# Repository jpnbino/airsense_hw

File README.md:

# Air Sense - Hardware

O projeto Air Sense foi desenvolvido para medir a qualidade do ar em centros urbanos. Para isso hardware desenvolvido conta com uma série de sensores capazes de identificar certos tipos de gases no ambiente, tais como, CO e NO2.

Este repositório contém os arquivos fontes do projeto de Hardware.

---

## Detalhes de Hardware

|  Item           |Descrição |
|-----------------|------------|
| Tensão de entrada   |  9V - 25V    |
| Tamanho da placa      | 16.5mm x 31mm|
| Controlador principal            | STM32F108 |
| Módulo GSM       | SIM800L            |
| Sensor de umidade, temperatura e pressão       | BME280            |
| Sensor de CO, NO2 e NH3        | MICS 6814            |

---

## Versão

V1I1 - Versão Inicial.

---

## Equipe

Rauhe - [rauhe.abdelhamid@gmail.com]()

João Paulo - [jpnogg@gmail.com]()

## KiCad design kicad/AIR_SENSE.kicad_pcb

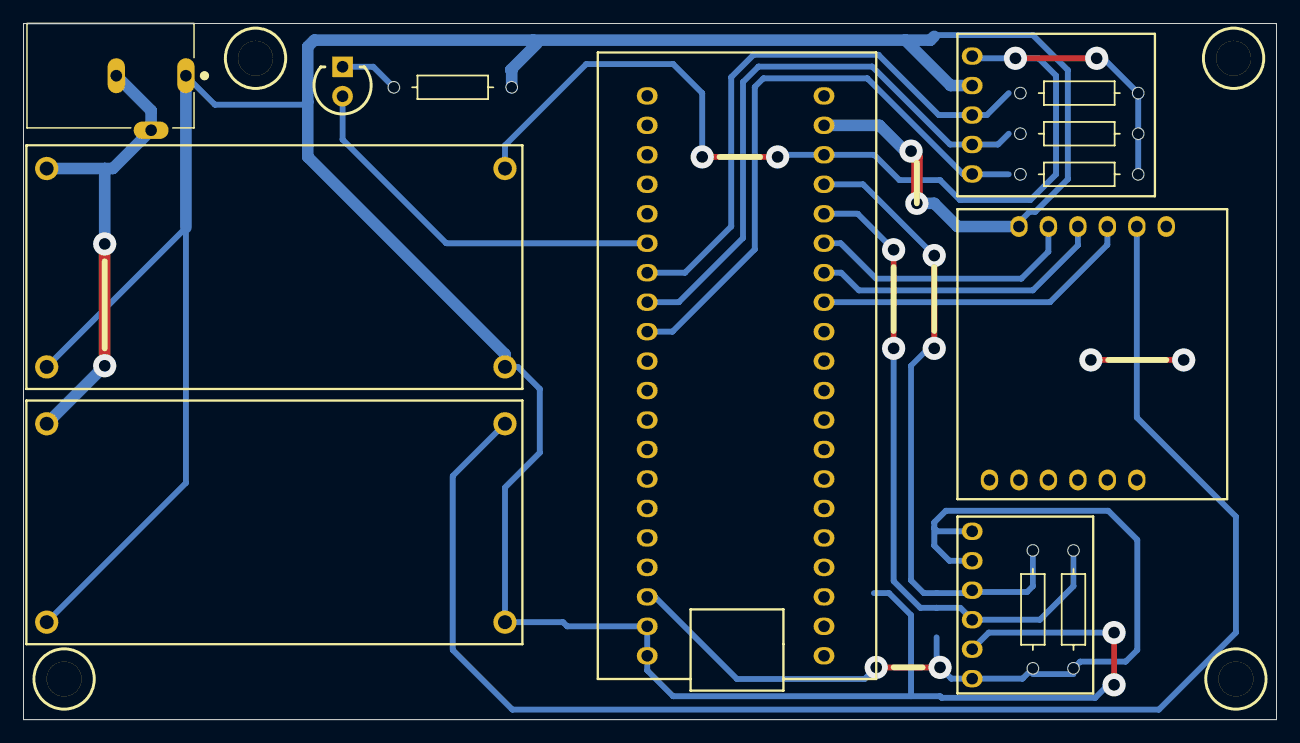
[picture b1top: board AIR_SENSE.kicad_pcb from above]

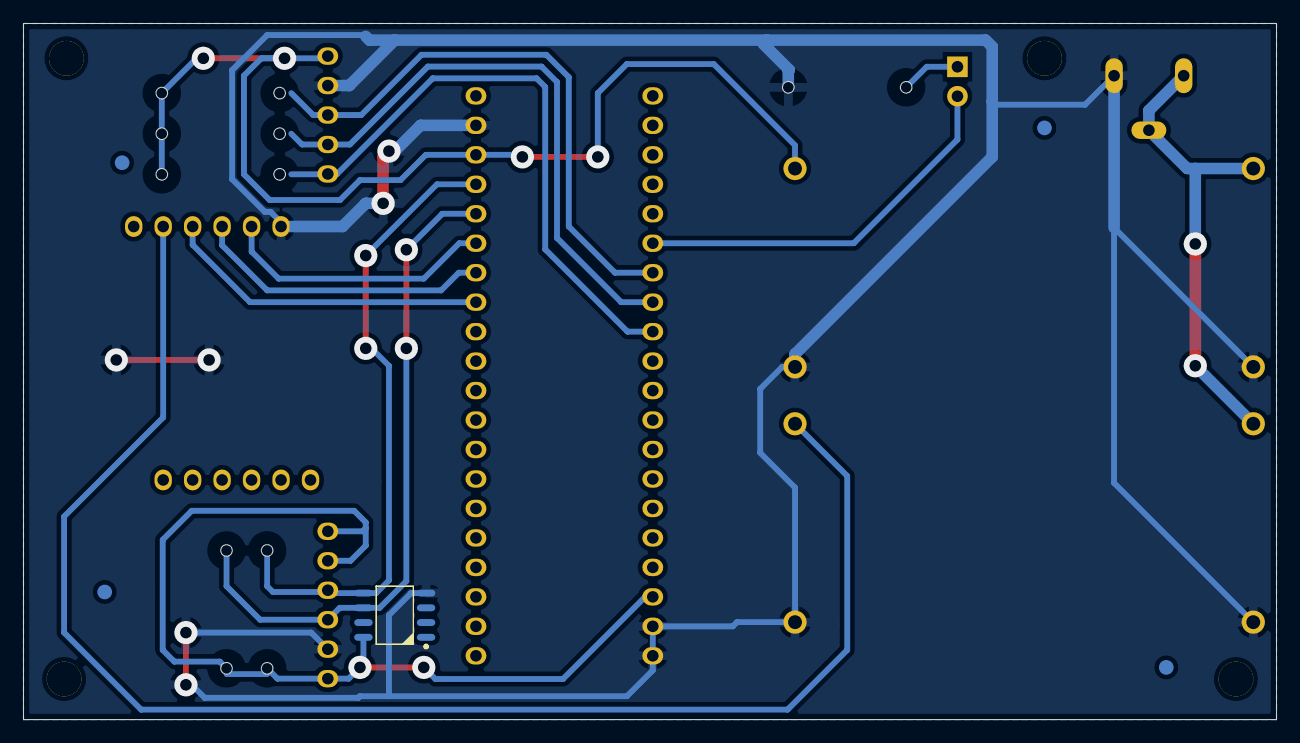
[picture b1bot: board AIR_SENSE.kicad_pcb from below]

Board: 2 copper layers, 108.0 x 60.0 mm, 19 parts (5 on the bottom side), 14 nets.

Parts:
FID1, FID2, FID3, FID4: FIDUCIAL; FIDUCIAL - 1.27mm
J1: MODULE BLUE PILL SOCKET
J2, J3: XL6009; MODULE DC-DC XL6009 SOCKET
J4: MODULE MICS6814 SOCKET
J5: MODULE SIM800L SOCKET
J6: Socket; MODULE BME280 SOCKET
J7: PJ-102BH; CUI_PJ-102BH
LED1: LED_RED_3MM_PTH; LED-3MM-RED
R1, R2, R3, R4, R5, R6: Carbon Film; RESTH_AXIAL-0.4
U1: Authentication Chip; SOIC127P600X175-8AN

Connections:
CO_VALUE: J1.29, J4.1
GND: J1.19, J1.39, J1.40, J2.2, J2.3, J3.2, J3.3, J4.4, J5.6, J6.5, J7.1, U1.4
I2C_SCL: J1.16, J6.4, U1.6
I2C_SDA: J1.17, J6.3, U1.5
NH3_VALUE: J1.28, J4.2
NO2_VALUE: J1.27, J4.3
PWM_1: J1.26, LED1.A
SIM800_RST: J1.13, J5.3
SIM800_RXD: J1.14, J5.4
SIM800_TXD: J1.15, J5.5
VCC3V3: J1.38, J6.1, J6.2, J6.6, U1.8
VCC4V0: J2.4, J5.2
VCC5V0: J1.18, J3.4, J4.5
Vin: J2.1, J3.1, J7.2, J7.3

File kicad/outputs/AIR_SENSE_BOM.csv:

"Reference","Value","Footprint","Qty","Manufacturer","MPN"
"J1","MODULE BLUE PILL SOCKET","airsense_lib:MODULE BLUE PILL SOCKET","1","",""
"J2,J3","MODULE DC-DC XL6009 SOCKET","airsense_lib:MODULE DC-DC XL6009 SOCKET","2","",""
"J4","MODULE MICS6814 SOCKET","airsense_lib:MODULE MICS6814 SOCKET","1","",""
"J5","MODULE SIM800L SOCKET","airsense_lib:MODULE SIM800L SOCKET","1","",""
"J6","MODULE BME280 SOCKET","airsense_lib:MODULE BME280 SOCKET","1","Sullins Connector Solutions","PPPC061LFBN-RC"
"J7","PJ-102BH","airsense_lib:CUI_PJ-102BH","1","CUI Inc.","PJ-102BH"
"LED1","LED_RED_3MM_PTH","airsense_lib:LED-3MM-RED","1","Marktech Optoelectronics","MT1403-RG-A"
"M1","Blue Pill","","1","",""
"M2,M3","XL6009","","2","",""
"M4","MICS6814","","1","",""
"M5","SIM800L","","1","",""
"M6","BME280","","1","",""
"R1-R6","12k","airsense_lib:RESTH_AXIAL-0.4","6","",""
"U1","ATECC608","airsense_lib:SOIC127P600X175-8AN","1","Microchip Technology","ATECC608A-SSHDA-T"
